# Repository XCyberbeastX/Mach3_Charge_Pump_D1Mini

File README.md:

# Mach3_Charge_Pump_D1Mini(ESP8266)

## Note:
This project is based on this [YouTube video](https://www.youtube.com/watch?v=voYk2AVyjqQ). Please be aware that I am not a professional circuit board designer and this information is shared from a hobbyist's perspective. Implementing this project is at your own risk, and it's advised to consult with a professional if needed.

## Info:
The charge pump circuit prevents the spindle from unintentionally starting while not using Mach3 with a parallel port. Especially during power up or down of the pc, this can lead to the parallel port outputs being switched randomly, posing a safety risk. The circuit, reads the 25/12,5 Khz signal of Mach3 and enables/disables the machine via a relay.

The Webinterface of the D1Mini (ESP8266) provides a easy way to read the charge pump frequency and relay state and can be further extended as needed.

The D1 Mini can be flashed using OTA through the 'ip/update' page after the first inital flash.

## 

*Make sure to enable the charge pump feature in Mach3 and assign a free pin.*

## Screenshots

*Website image*

*finished PCB for THT-Soldering, with bigger pads*

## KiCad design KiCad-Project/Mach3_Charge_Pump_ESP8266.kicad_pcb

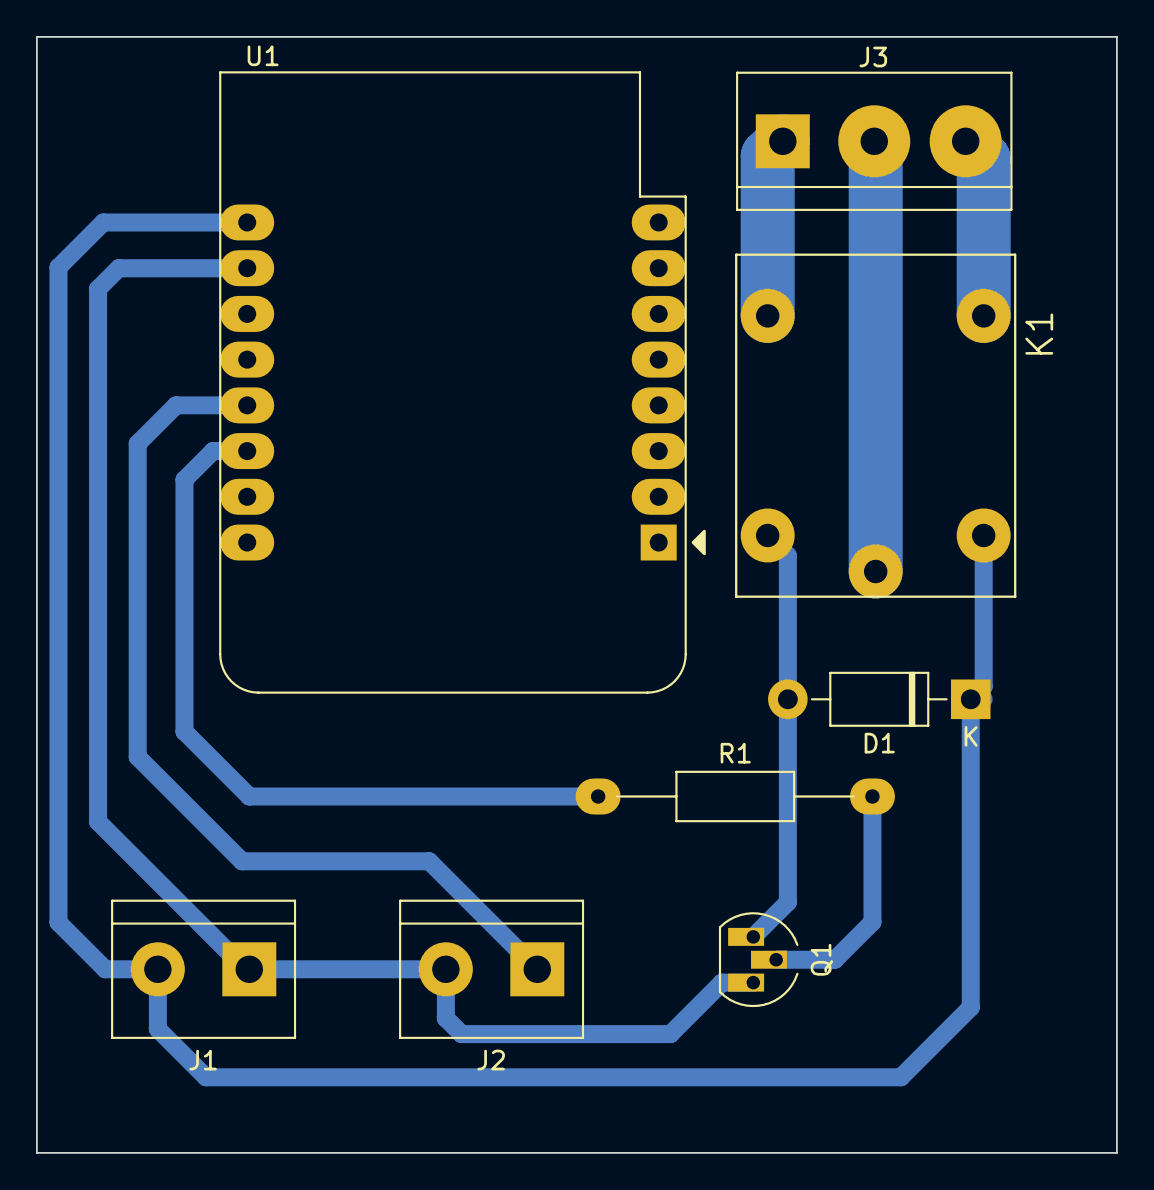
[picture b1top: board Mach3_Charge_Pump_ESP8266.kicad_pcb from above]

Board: 2 copper layers, 60.0 x 62.0 mm, 8 parts (0 on the bottom side), 9 nets.

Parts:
D1: 1N4007; D_DO-41_SOD81_P10.16mm_Horizontal
J1: Voltage-IN; TerminalBlock_bornier-2_P5.08mm
J2: CP-Signal & PP-GND; TerminalBlock_bornier-2_P5.08mm
J3: Relay-Output; TerminalBlock_bornier-3_P5.08mm
K1: JQC-3F-1C-24VDC; RELAY_JQC-3F-1C-24VDC
Q1: BC547; TO-92L_HandSolder
R1: 4,7K; R_Axial_DIN0207_L6.3mm_D2.5mm_P15.24mm_Horizontal
U1: WeMos_D1_mini; WEMOS_D1_mini_light

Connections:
+5V: D1.1 (K), J1.2, K1.COIL1, U1.9 (5V)
GND: J1.1, J2.2, Q1.3 (E), U1.10 (GND)
unnamed: D1.2 (A), K1.COIL2, Q1.1 (C)
unnamed: J2.1, U1.13 (SDA/D2)
unnamed: J3.1, K1.NC
unnamed: J3.2, K1.COM
unnamed: J3.3, K1.NO
unnamed: Q1.2 (B), R1.2
unnamed: R1.1, U1.14 (SCL/D1)

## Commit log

2023-12-28 Project setup: Added gitignore and README
2023-12-28 Added D1Mini Arduino code and image for readme
2023-12-28 Code style improvements
2023-12-28 Added D1Mini Website image
2023-12-30 Added KiCad Project + restructured repo
